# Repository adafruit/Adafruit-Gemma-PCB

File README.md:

## Adafruit Gemma Classic (ATtiny85) PCB
<a href="http://www.adafruit.com/products/1222"><br/>
Click here to purchase one from the Adafruit shop</a>

Deprecation Warning: The Gemma bit-bang USB technique it uses doesn't work as well as it did in 2014, many modern computers won't work well. So while we still carry the Gemma so that people can maintain some older projects, we no longer recommend it. Please check out the Gemma M0. It has built-in USB, more capabilities, and is comparable in price!

GEMMA is a tiny wearable platform board with a lot of might in a 1" diameter package. Powered by a Attiny85 and programmable with an Arduino IDE over USB, you'll be able to realize any wearable project!

We wanted to design a microcontroller board that was small enough to fit into any project, and low cost enough to use without hesitation. Perfect for when you don't want to give up your Flora and you aren't willing to take apart the project you worked so hard to design. It's our lowest-cost sewable controller!

The Attiny85 is a fun processor because despite being so small, it has 8K of flash, and 5 I/O pins, including analog inputs and PWM 'analog' outputs. We designed a USB bootloader so you can plug it into any computer and reprogram it over a USB port just like an Arduino (it uses 2 of the 5 I/O pins, leaving you with 3). In fact we even made some simple modifications to the Arduino IDE so that it works like a mini-Flora. Perfect for small & simple projects the GEMMA will be your go-to wearable electronics platform.

This is the CAD & PCB data for the Adafruit Gemma. The PCB format is EagleCAD schematic and board layout

For more details, check out the product page at
- https://www.adafruit.com/products/1222

### License

Adafruit invests time and resources providing this open source design, please support Adafruit and open-source hardware by purchasing products from [Adafruit](https://www.adafruit.com)!

All text above must be included in any redistribution

Designed by Limor Fried/Ladyada for Adafruit Industries.
Creative Commons Attribution/Share-Alike, all text above must be included in any redistribution. 
See license.txt for additional information.

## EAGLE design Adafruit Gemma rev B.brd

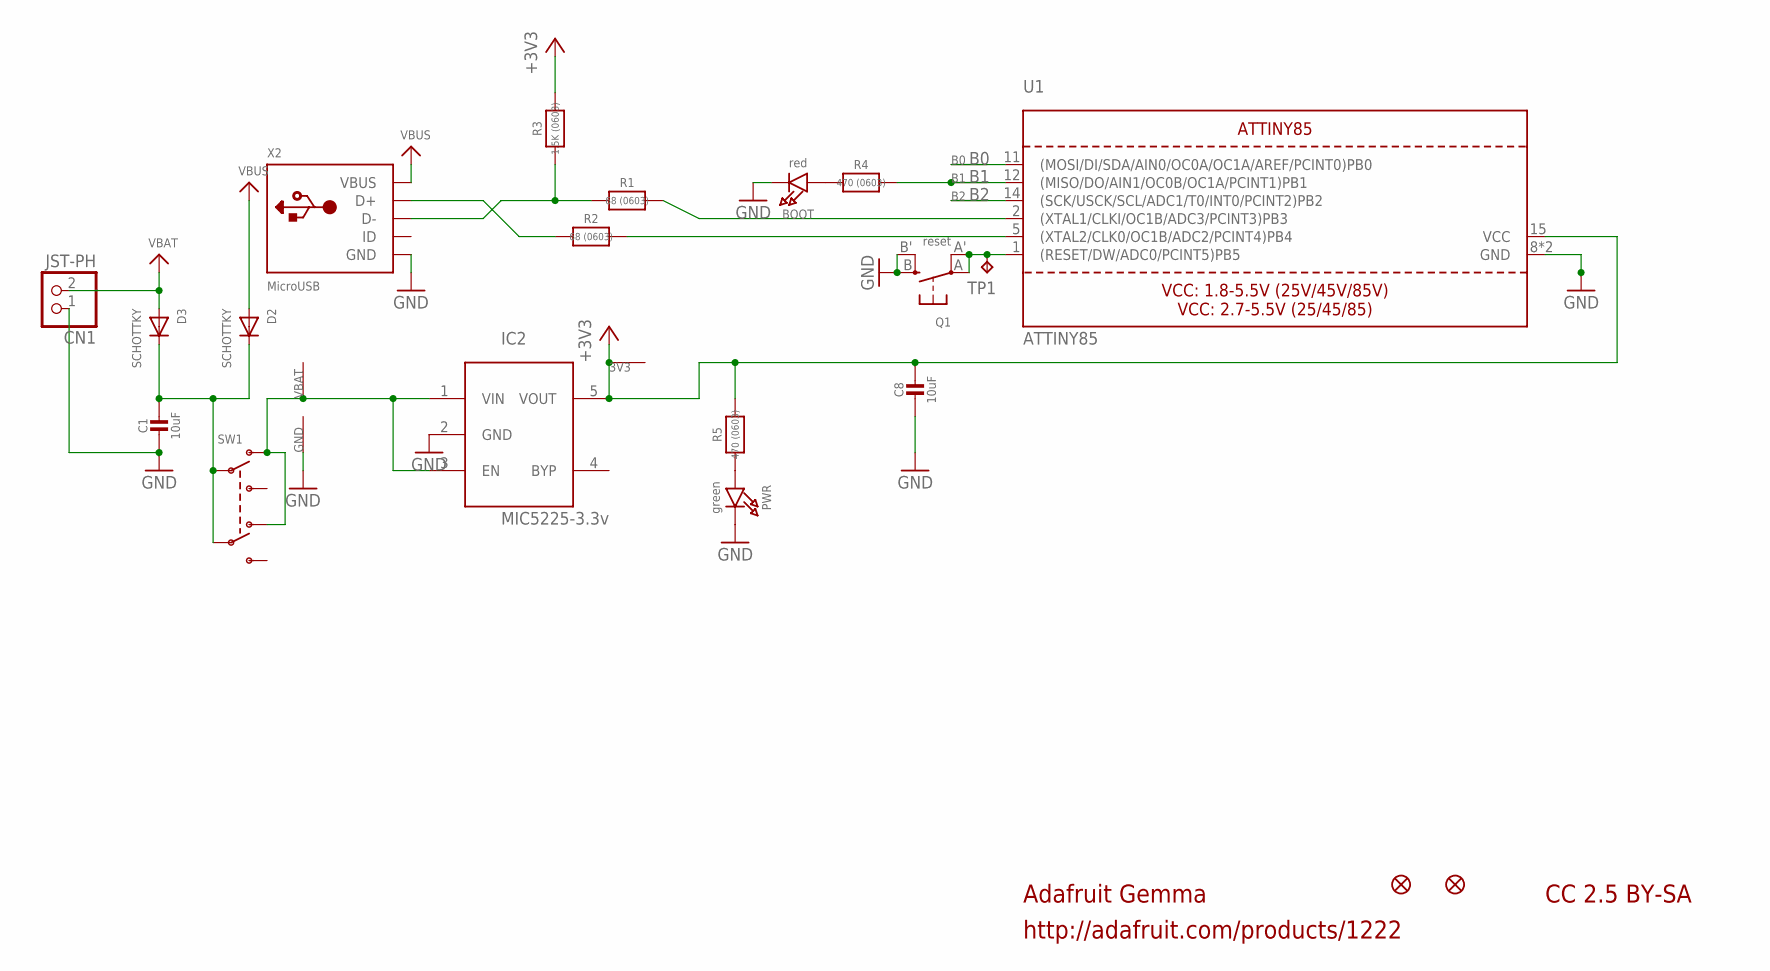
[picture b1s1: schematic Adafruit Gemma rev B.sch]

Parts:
3V3: SEWTAP-2.0IN; SEWINGTAP_2.0
B0, B1, B2: SEWTAP-2.0IN; SEWINGTAP_2.0
BOOT: red; CHIPLED_0805_NOOUTLINE
C1, C8: 10uF; 0805-NO
CN1: JST-PH; JSTPH2
D2, D3: SCHOTTKY; SOD-123FL
GND: SEWTAP-2.0IN; SEWINGTAP_2.0
IC2: MIC5225-3.3v; SOT23-5L
PWR: green; CHIPLED_0805_NOOUTLINE
Q1: reset; BTN_KMR2_4.6X2.8
R1, R2: 68 (0603); 0603-NO
R3: 1.5K (0603); 0603-NO
R4, R5: 470 (0603); 0603-NO
SW1: SWITCH_DPDTEG1390; EG1390
TP1: TPB2,54; B2,54
U1: ATTINY85; MLF20_4X4MM_0.5MM_ATMEL
U$1, U$6: FIDUCIAL""; FIDUCIAL_1MM
VBAT: SEWTAP-2.0IN; SEWINGTAP_2.0
X2: MicroUSB; 4UCONN_20329

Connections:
+3V3: 3V3.P$1, C8.1, IC2.5 (VOUT), R3.2, R5.2, U1.15 (VCC)
B0: B0.P$1, U1.11 ((MOSI/DI/SDA/AIN0/OC0A/OC1A/AREF/PCINT0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)
B1: B1.P$1, R4.2, U1.12 ((MISO/DO/AIN1/OC0B/OC1A/PCINT1)PB1)
B2: B2.P$1, U1.14 ((SCK/USCK/SCL/ADC1/T0/INT0/PCINT2)PB2)
GND: BOOT.C, C1.2, C8.2, CN1.1, GND.P$1, IC2.2 (GND), PWR.C, Q1.B (S), Q1.B' (S1), U1.8 (GND), U1.THERMAL (GND), X2.BASE@1 (GND), X2.BASE@2 (GND), X2.GND, X2.SPRT@1 (GND), X2.SPRT@2 (GND), X2.SPRT@3 (GND), X2.SPRT@4 (GND)
unnamed: Q1.A, Q1.A' (P1), TP1.TP, U1.1 ((RESET/DW/ADC0/PCINT5)PB5)
unnamed: R2.1, X2.D+
unnamed: R1.2, U1.2 ((XTAL1/CLKI/OC1B/ADC3/PCINT3)PB3)
unnamed: R2.2, U1.5 ((XTAL2/CLK0/OC1B/ADC2/PCINT4)PB4)
unnamed: R1.1, R3.1, X2.D-
unnamed: BOOT.A, R4.1
unnamed: IC2.1 (VIN), IC2.3 (EN), SW1.O1, SW1.O2, VBAT.P$1
unnamed: PWR.A, R5.1
unnamed: C1.1, D2.C, D3.C, SW1.P1, SW1.P2
VBAT: CN1.2, D3.A
VBUS: D2.A, X2.VBUS

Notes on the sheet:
Adafruit Gemma
http://adafruit.com/products/1222
CC 2.5 BY-SA

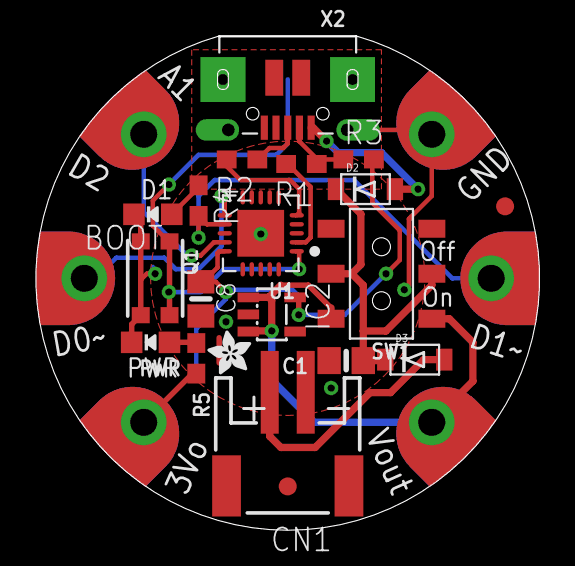
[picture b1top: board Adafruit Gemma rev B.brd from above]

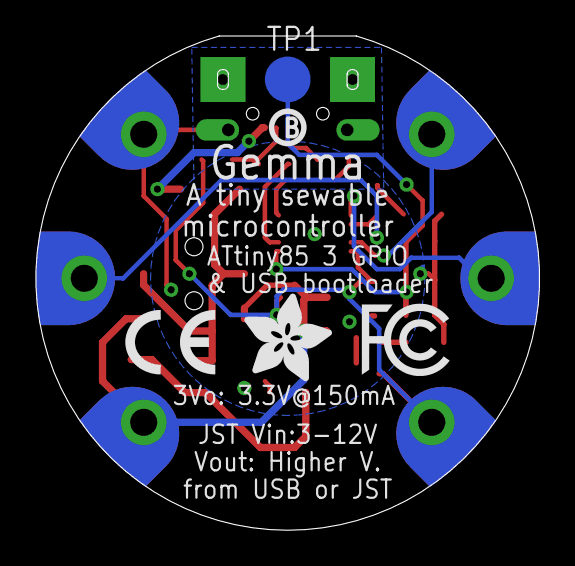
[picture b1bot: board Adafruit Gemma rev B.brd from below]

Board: 2 copper layers, 28.0 x 27.5 mm, 31 parts (5 on the bottom side), 16 nets.

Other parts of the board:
U$2: ADAFRUIT_2.5MM
U$7: ADAFRUIT_5MM
U$8: SYMBOL_FCC_5MM
U$9: SYMBOL_CE_5MM
U$10: PCBFEAT-REV-040

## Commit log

2014-10-14 init
2016-05-09 added v2!
2021-11-30 Added prettypins pinout file

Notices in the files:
parts and their libraries:
microbuilder: This work is placed in the public domain, and may be freely used for commercial and non-commercial work with the following conditions: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
